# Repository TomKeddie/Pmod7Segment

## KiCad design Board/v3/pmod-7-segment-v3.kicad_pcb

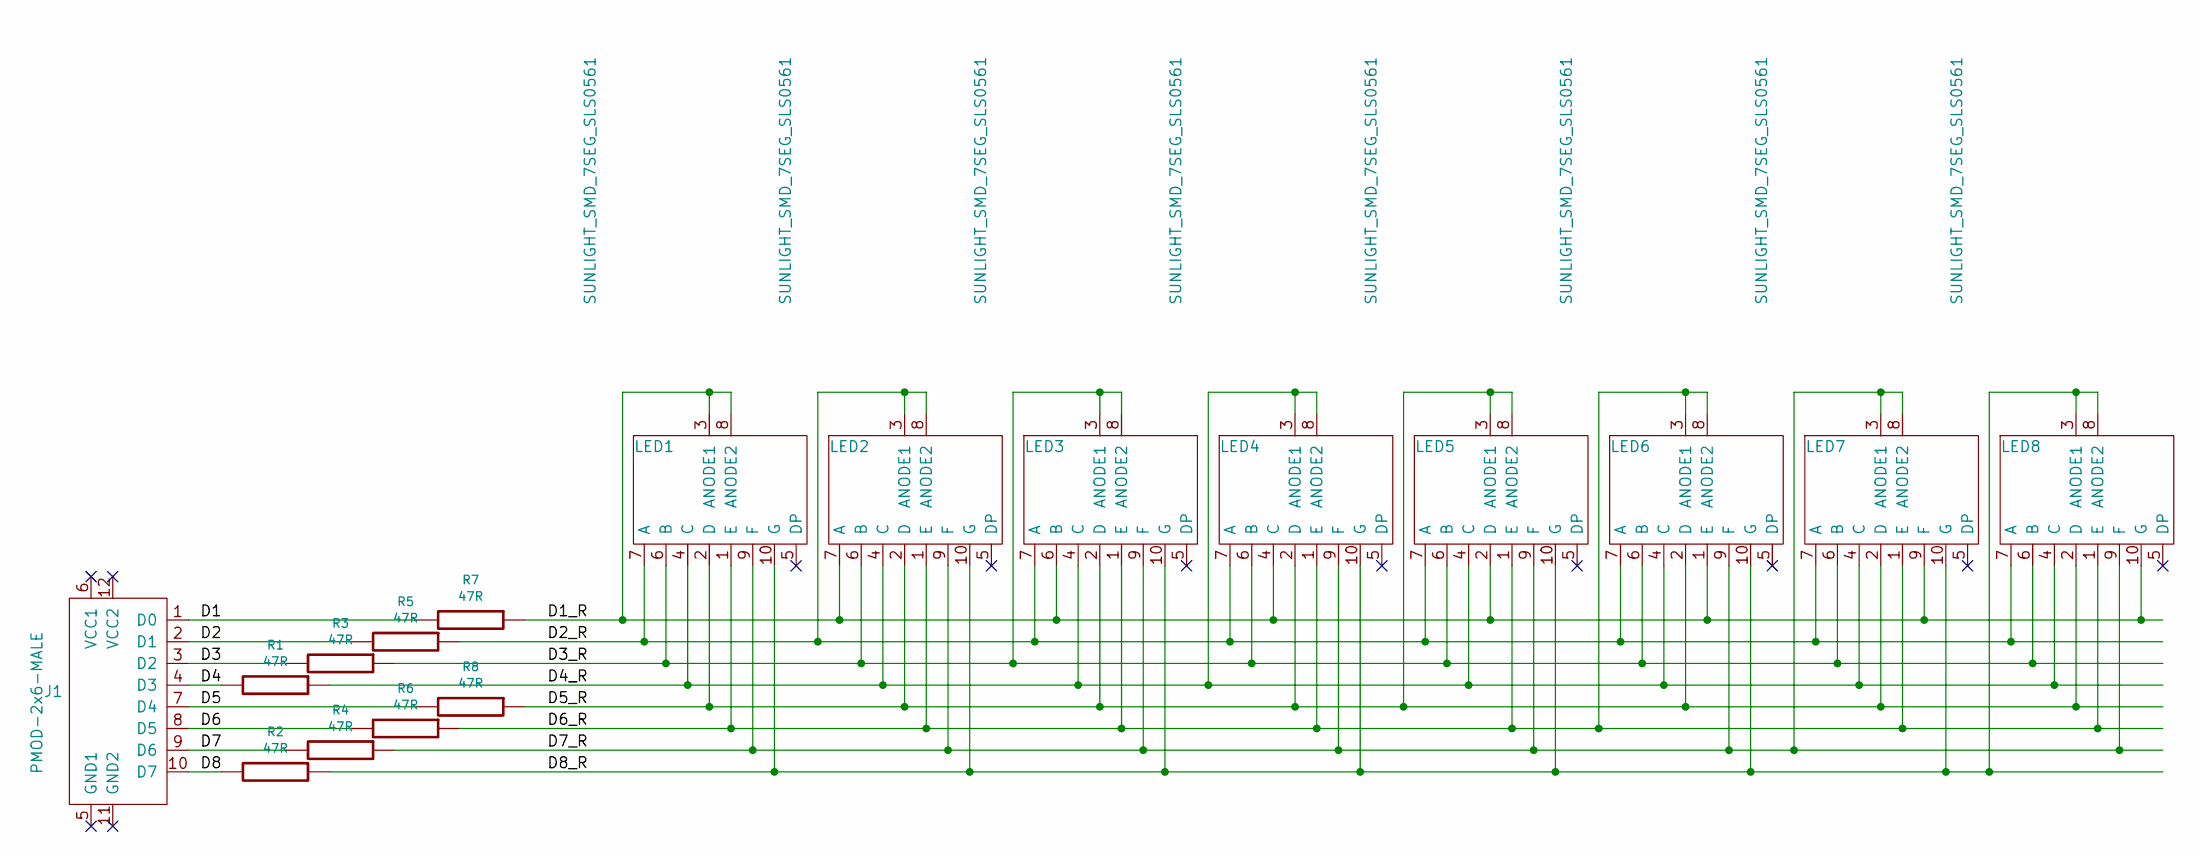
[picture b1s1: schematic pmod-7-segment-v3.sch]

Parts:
J1: PMOD-2x6-MALE; PMOD_2X6_PTH_RA_PLUG
LED1, LED2, LED3, LED4, LED5, LED6, LED7, LED8: SUNLIGHT_SMD_7SEG_SLS0561
R1, R2, R3, R4, R5, R6, R7, R8: 47R; R_0603_1608Metric

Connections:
/D1: J1.1 (D0), R7.2
/D1_R: LED1.3 (ANODE1), LED1.8 (ANODE2), LED2.7 (A), LED3.6 (B), LED4.4 (C), LED5.2 (D), LED6.1 (E), LED7.9 (F), LED8.10 (G), R7.1
/D2: J1.2 (D1), R5.2
/D2_R: LED1.7 (A), LED2.3 (ANODE1), LED2.8 (ANODE2), LED3.7 (A), LED4.7 (A), LED5.7 (A), LED6.7 (A), LED7.7 (A), LED8.7 (A), R5.1
/D3: J1.3 (D2), R3.2
/D3_R: LED1.6 (B), LED2.6 (B), LED3.3 (ANODE1), LED3.8 (ANODE2), LED4.6 (B), LED5.6 (B), LED6.6 (B), LED7.6 (B), LED8.6 (B), R3.1
/D4: J1.4 (D3), R1.2
/D4_R: LED1.4 (C), LED2.4 (C), LED3.4 (C), LED4.3 (ANODE1), LED4.8 (ANODE2), LED5.4 (C), LED6.4 (C), LED7.4 (C), LED8.4 (C), R1.1
/D5: J1.7 (D4), R8.2
/D5_R: LED1.2 (D), LED2.2 (D), LED3.2 (D), LED4.2 (D), LED5.3 (ANODE1), LED5.8 (ANODE2), LED6.2 (D), LED7.2 (D), LED8.2 (D), R8.1
/D6: J1.8 (D5), R6.2
/D6_R: LED1.1 (E), LED2.1 (E), LED3.1 (E), LED4.1 (E), LED5.1 (E), LED6.3 (ANODE1), LED6.8 (ANODE2), LED7.1 (E), LED8.1 (E), R6.1
/D7: J1.9 (D6), R4.2
/D7_R: LED1.9 (F), LED2.9 (F), LED3.9 (F), LED4.9 (F), LED5.9 (F), LED6.9 (F), LED7.3 (ANODE1), LED7.8 (ANODE2), LED8.9 (F), R4.1
/D8: J1.10 (D7), R2.2
/D8_R: LED1.10 (G), LED2.10 (G), LED3.10 (G), LED4.10 (G), LED5.10 (G), LED6.10 (G), LED7.10 (G), LED8.3 (ANODE1), LED8.8 (ANODE2), R2.1

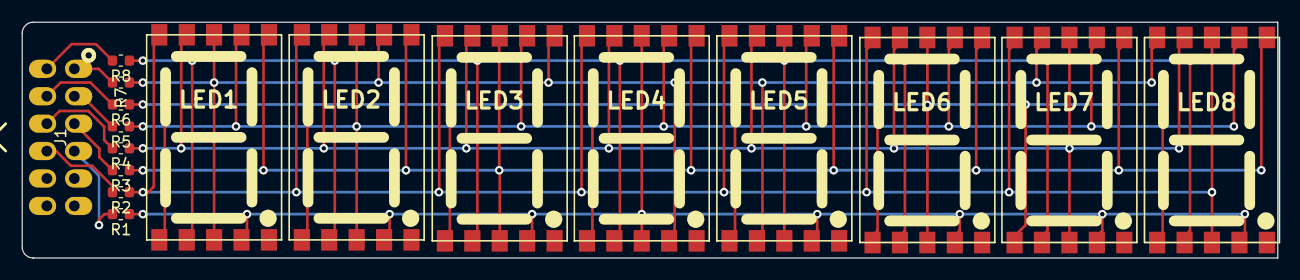
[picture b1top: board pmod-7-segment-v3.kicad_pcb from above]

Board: 2 copper layers, 116.3 x 21.8 mm, 17 parts (0 on the bottom side), 16 nets.

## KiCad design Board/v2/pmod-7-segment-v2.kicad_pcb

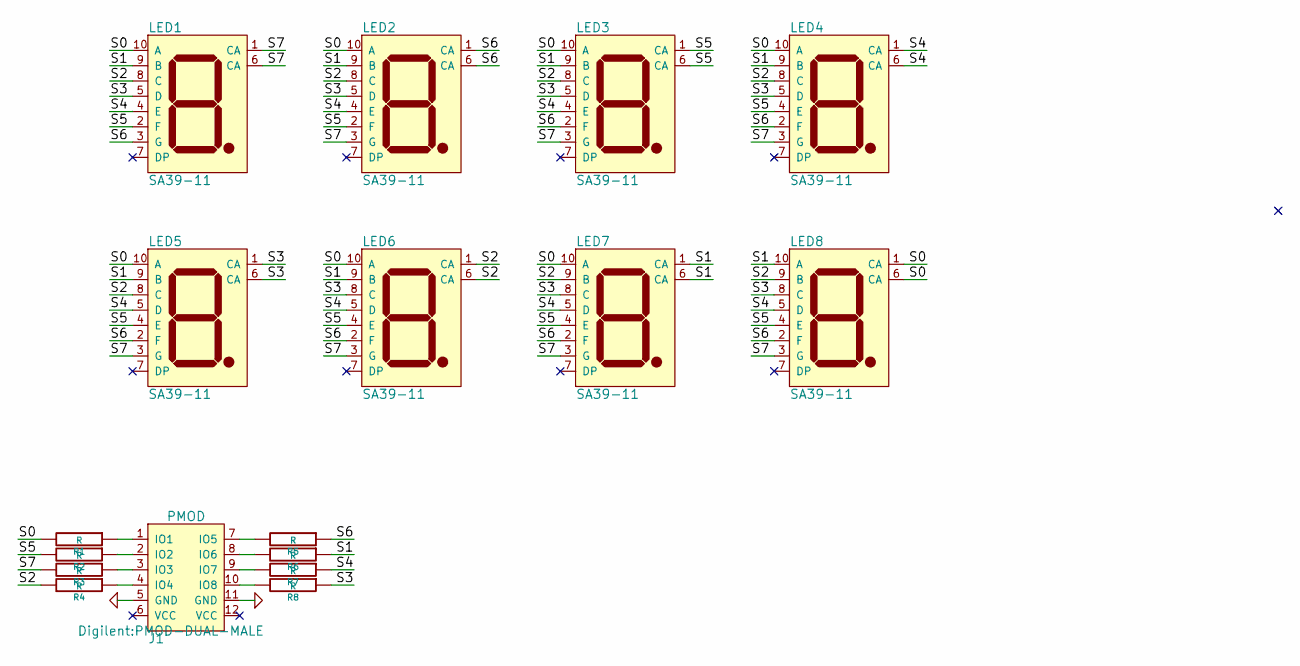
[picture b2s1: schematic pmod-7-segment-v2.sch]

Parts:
J1: PMOD; PMOD-DUAL-MALE
LED1, LED2, LED3, LED4, LED5, LED6, LED7, LED8: SA39-11; 10pcs-1bit-1-bit-Common-Anode-Positive-Digital-Tube-0-36-0-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
R1, R2, R3, R4, R5, R6, R7, R8: R; R_0603

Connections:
/IO1: LED1.10 (A), LED2.10 (A), LED3.10 (A), LED4.10 (A), LED5.10 (A), LED6.10 (A), LED7.10 (A), LED8.1 (CA), LED8.6 (CA), R1.2
/IO2: LED1.2 (F), LED2.2 (F), LED3.1 (CA), LED3.6 (CA), LED4.4 (E), LED5.4 (E), LED6.4 (E), LED7.4 (E), LED8.4 (E), R2.2
/IO3: LED1.1 (CA), LED1.6 (CA), LED2.3 (G), LED3.3 (G), LED4.3 (G), LED5.3 (G), LED6.3 (G), LED7.3 (G), LED8.3 (G), R3.2
/IO4: LED1.8 (C), LED2.8 (C), LED3.8 (C), LED4.8 (C), LED5.8 (C), LED6.1 (CA), LED6.6 (CA), LED7.9 (B), LED8.9 (B), R4.2
/IO5: LED1.3 (G), LED2.1 (CA), LED2.6 (CA), LED3.2 (F), LED4.2 (F), LED5.2 (F), LED6.2 (F), LED7.2 (F), LED8.2 (F), R5.1
/IO6: LED1.9 (B), LED2.9 (B), LED3.9 (B), LED4.9 (B), LED5.9 (B), LED6.9 (B), LED7.1 (CA), LED7.6 (CA), LED8.10 (A), R6.1
/IO7: LED1.4 (E), LED2.4 (E), LED3.4 (E), LED4.1 (CA), LED4.6 (CA), LED5.5 (D), LED6.5 (D), LED7.5 (D), LED8.5 (D), R7.1
/IO8: LED1.5 (D), LED2.5 (D), LED3.5 (D), LED4.5 (D), LED5.1 (CA), LED5.6 (CA), LED6.8 (C), LED7.8 (C), LED8.8 (C), R8.1
GND: J1.5 (GND), J1.11 (GND)
unnamed: J1.1 (IO1), R1.1
unnamed: J1.2 (IO2), R2.1
unnamed: J1.3 (IO3), R3.1
unnamed: J1.4 (IO4), R4.1
unnamed: J1.7 (IO5), R5.2
unnamed: J1.8 (IO6), R6.2
unnamed: J1.9 (IO7), R7.2
unnamed: J1.10 (IO8), R8.2

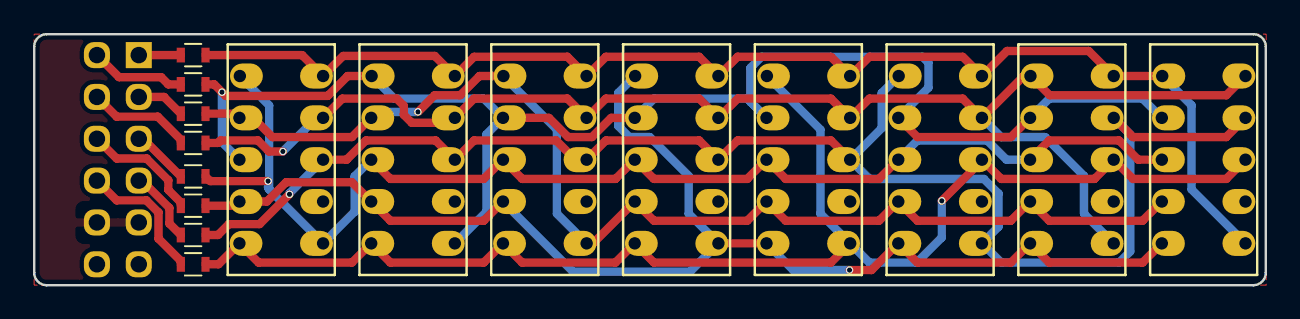
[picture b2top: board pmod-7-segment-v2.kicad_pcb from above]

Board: 2 copper layers, 74.8 x 15.2 mm, 17 parts (0 on the bottom side), 17 nets.

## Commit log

2019-07-12 first pass at v2 - using 7 segment displays from Aliexpress
2019-08-21 v2 updates
2019-08-21 v2.0 routed and DRC ok, ready for mfg
2019-08-21 Silk fixes
2019-09-09 pmod-7-segment-v2 : v2.1 as submitted to oshpark
2019-10-27 v2: renumber nets, fix SolderMaskClearance, fix copper pour isolation, v2.2
2019-10-29 v2: update solder mask clearance to 0.0508
2019-11-18 pmod-7-segment-v3: initial version
2019-11-19 v3: initial schematic
2019-11-19 v3: v3.0 as sent to jlcpcb
